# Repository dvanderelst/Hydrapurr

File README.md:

# HydraPurr

> **Running the test device?** See the tester guide:
> [`firmware/README.md`](firmware/README.md) (set-up, the screen, getting the data).

A CircuitPython device that monitors cat drinking at a water bowl. It records every touch on a wire in the water and the water level, 100 times a second, so licks and drinking bouts can be found from the data. The longer-term goal is to dispense food once a cat has completed enough drinking bouts.

(An earlier prototype, on an RP2040 board with a transistor lick circuit, RFID and live bout detection, is kept under [`legacy/`](legacy/); its firmware is documented in [`legacy/v1_firmware/README.md`](legacy/v1_firmware/README.md).)

## Project layout

```
HydraPurr/
├── HANDOFF.md    Development notes, open items and log (whole project).
├── firmware/     The device's CircuitPython code. README.md = tester guide.
├── analysis/     Data processing: fetch from the board, read, plot (own .venv).
├── pcb/          Carrier PCB (KiCad): board stack, feeder driver, connectors.
├── sync2board    Push the firmware to a connected board.
├── legacy/       The first prototype: v1_firmware/ (was BoardCode/),
│                 ProcessLickData/, CircuitSimulation/, HardwareDocs/,
│                 BluetoothDownloader/, todo.md.
└── README.md     This file.
```

## Hardware

Adafruit Feather ESP32-S3 Reverse TFT (built-in screen, WiFi) on an Adalogger FeatherWing (microSD, PCF8523 RTC), CircuitPython 10.3.1. Details, pin map and the reasoning behind each choice: [`HANDOFF.md`](HANDOFF.md).

- **Touch sensor:** a wire in the water on `D12`, read with `touchio`. A tongue (or finger) in the water raises the reading well above a slowly tracking baseline. Touching the outside of the 3D-printed resin bowl registers too, but much weaker.
- **Water level:** a float in a chimney connected to the bowl; a Sharp GP2Y0A51SK0F IR distance sensor above it on `A5` (0.62 V empty to 1.16 V full in the current bowl).
- **Contact LED** on `D9` (lit while touched; for video checks).
- **WiFi:** joins the first configured network in range; serves the SD card at `http://hydrapurr.local/`, sets its clock from NTP, and sends a heartbeat to healthchecks.io every 15 min.
- **Planned:** a carrier PCB (`pcb/`) with a 12 V boost and MOSFET driver for a feeder; bout detection and feeding back on the board (the code is in `firmware/lib/BoutDetection.py`).

## Data

The board writes hourly raw files (`raw/<date>/<hour>.csv`, every sample: touch, baseline, contact, water) and a daily events file (`events/<date>.csv`: one row per contact, a status row every 15 min, restarts, settings) to its SD card, plus `system.log`. Columns: `firmware/lib/RawRecorder.py` and `firmware/lib/EventLog.py`. Reading, fetching and plotting: [`analysis/readme.md`](analysis/readme.md).

## Development

- **Syncing code to the board:** `./sync2board firmware` — `rsync` to the mounted CIRCUITPY drive (`/media/$USER/CIRCUITPY` by default; `-d` for another path, `-n` dry run). Mirrors with `--delete` but never touches the board's `settings.toml`; excludes Python caches and editor metadata, runs `sync` afterwards. Once WiFi has been used the board does not auto-reload: press Reset (or send Ctrl-C) after syncing.
- **`analysis/`** is desktop Python — create its `.venv` from `requirements.txt` (see its readme). Entry point: `plot_hydrapurr_day.py`. Data lives in `analysis/data/v2_esp32s3_touch/` (not in git; with a README on what it holds).
- **CircuitPython `lib/` convention.** CircuitPython auto-adds `/` and `/lib` to `sys.path` on boot, so any `.py` file or package directory directly under `lib/` is importable as a top-level module (`import adafruit_pcf8523`, `from components import MySD`). Do **not** add `lib/__init__.py` — that turns `lib` into a package and breaks the standard CircuitPython import style. To get the same behaviour in PyCharm during desktop development, mark `lib/` as a Sources Root (Right-click → *Mark Directory as → Sources Root*).

## Project notes

- Notion workspace for organisation: <https://www.notion.so/PyCharm-25581ad79c6d8070aaf2cc3cb64adce6>
- The older Raspberry Pi version of HydraPurr is archived (read-only reference): <https://github.com/habit-tech/Rpi_lickometer>.

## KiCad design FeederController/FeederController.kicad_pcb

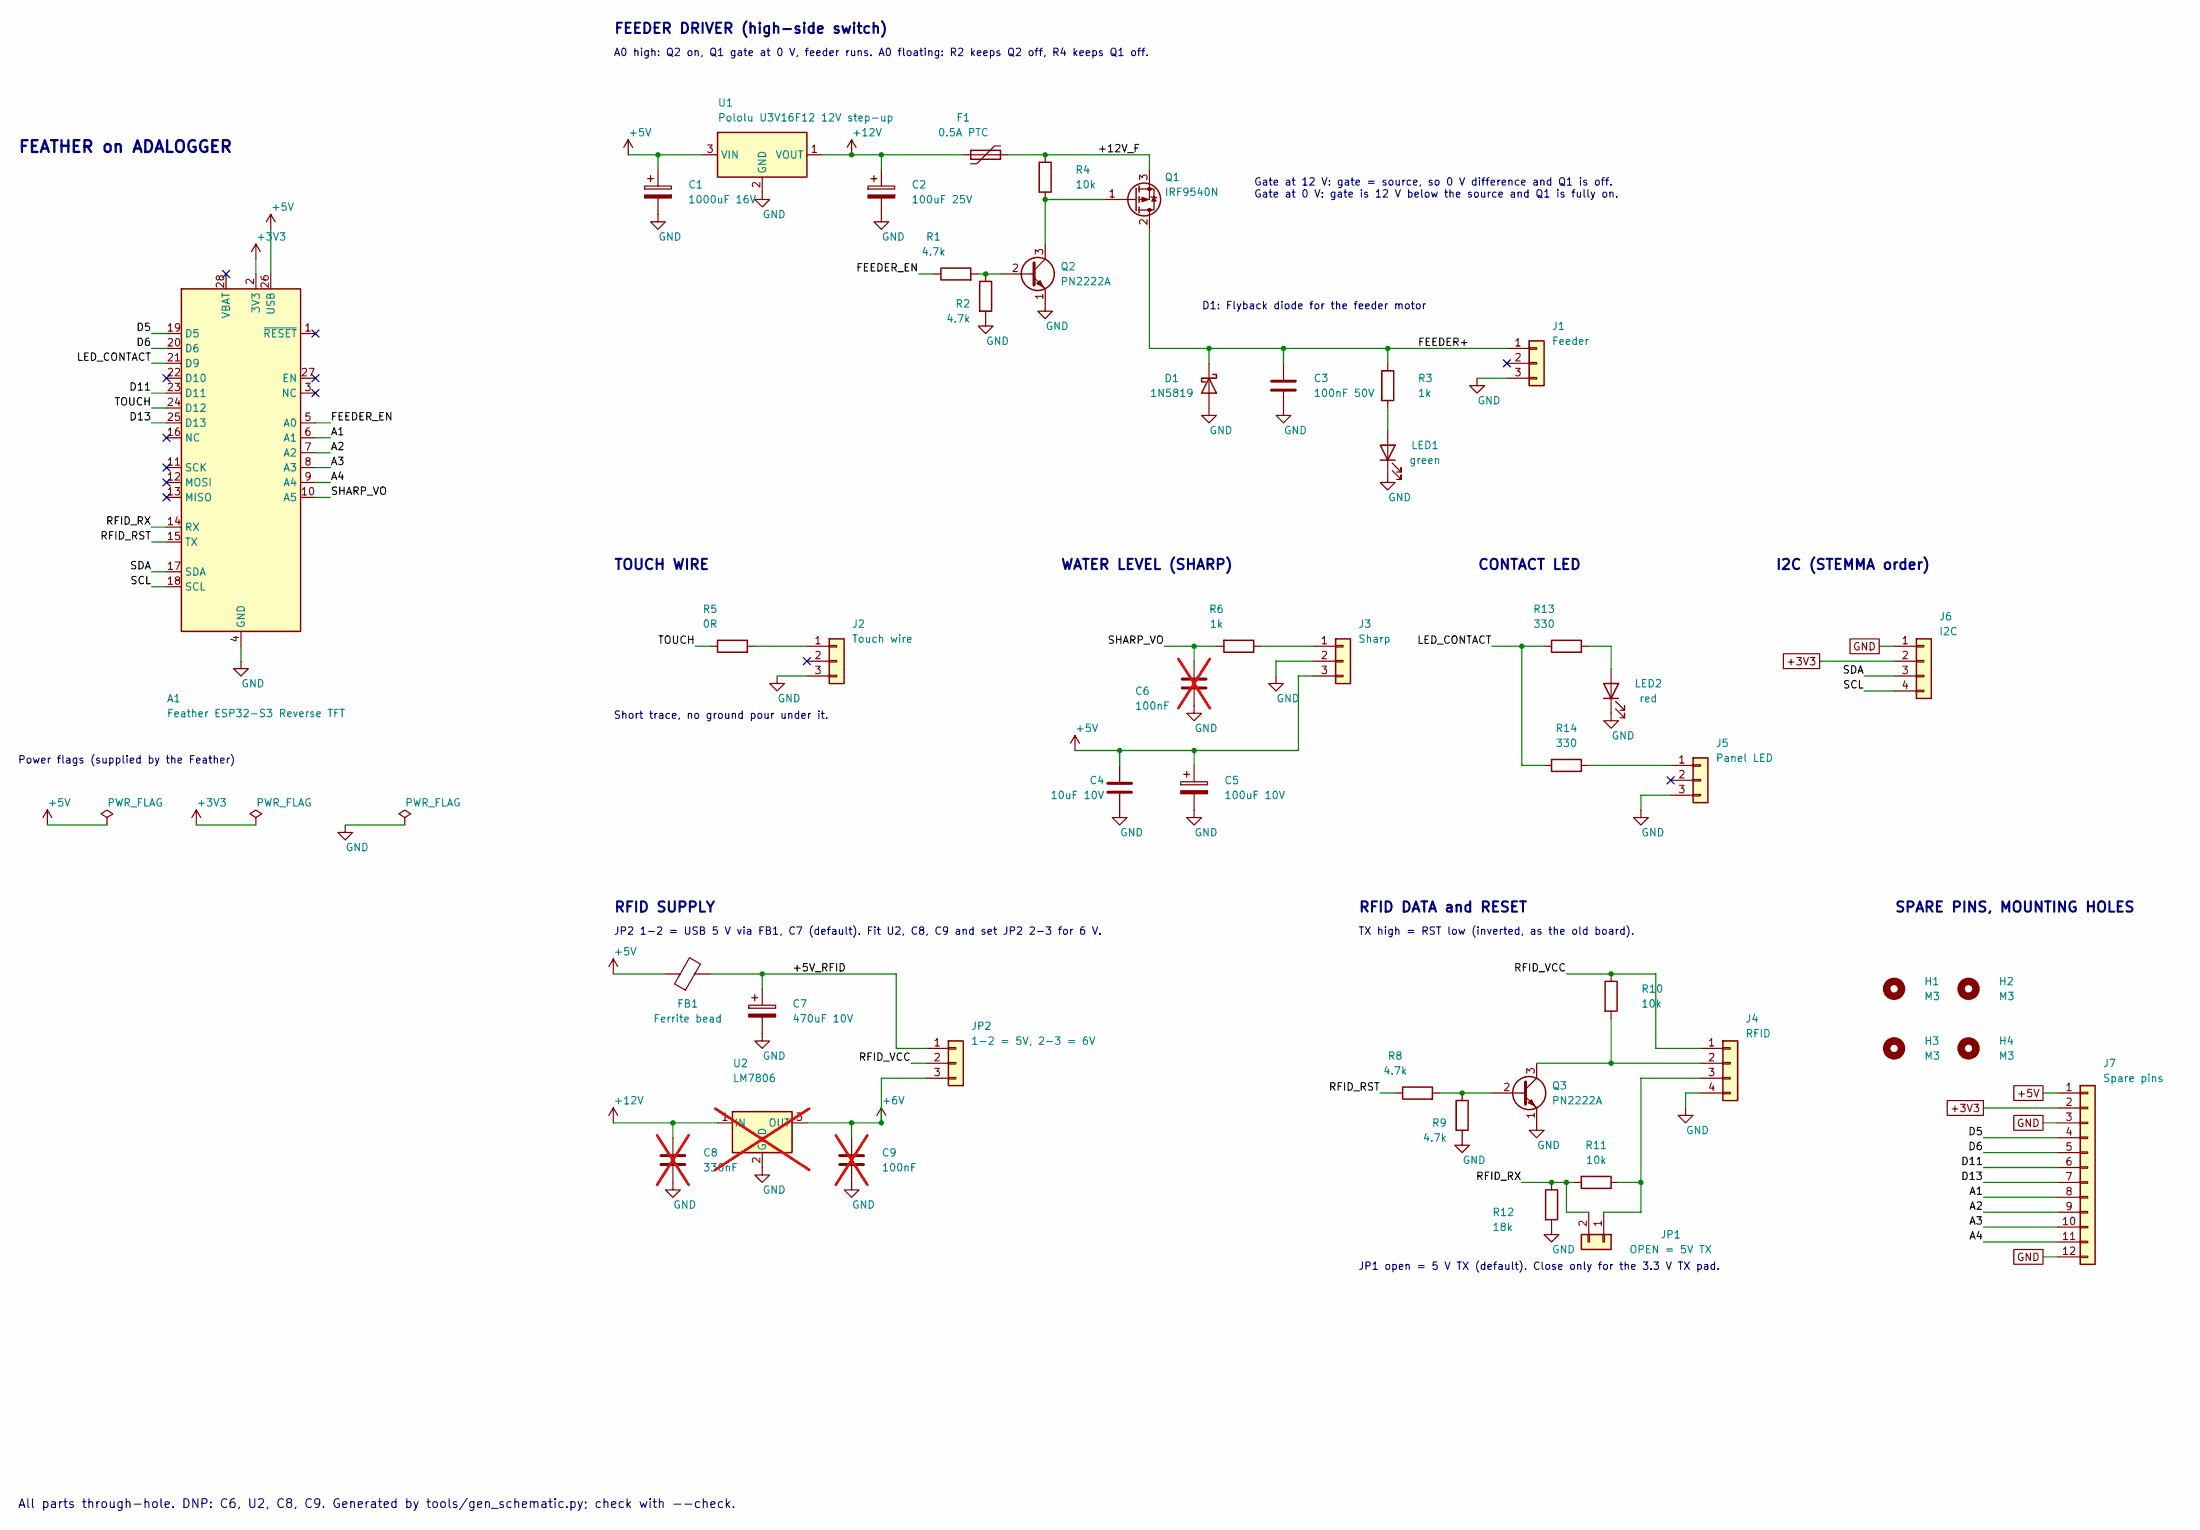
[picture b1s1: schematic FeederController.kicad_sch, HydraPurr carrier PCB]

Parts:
A1: Feather ESP32-S3 Reverse TFT; Feather_Adalogger_Inverted_Stack
C1: 1000uF 16V; CP_Radial_D10.0mm_P5.00mm
C2: 100uF 25V; CP_Radial_D6.3mm_P2.50mm
C3: 100nF 50V; C_Disc_D5.0mm_W2.5mm_P5.00mm
C4: 10uF 10V; C_Disc_D5.0mm_W2.5mm_P5.00mm
C5: 100uF 10V; CP_Radial_D6.3mm_P2.50mm
C6, C9: 100nF; C_Disc_D5.0mm_W2.5mm_P5.00mm; not fitted
C7: 470uF 10V; CP_Radial_D8.0mm_P3.50mm
C8: 330nF; C_Disc_D5.0mm_W2.5mm_P5.00mm; not fitted
D1: 1N5819; D_DO-41_SOD81_P10.16mm_Horizontal
F1: 0.5A PTC; Fuse_Bourns_MF-RHT050
FB1: Ferrite bead; L_Axial_L5.3mm_D2.2mm_P10.16mm_Horizontal_Vishay_IM-1
H1, H2, H3, H4: M3; MountingHole_3.2mm_M3
J1: Feeder; JST_PH_B3B-PH-K_1x03_P2.00mm_Vertical
J2: Touch wire; JST_PH_B3B-PH-K_1x03_P2.00mm_Vertical
J3: Sharp; JST_PH_B3B-PH-K_1x03_P2.00mm_Vertical
J4: RFID; JST_PH_B4B-PH-K_1x04_P2.00mm_Vertical
J5: Panel LED; JST_PH_B3B-PH-K_1x03_P2.00mm_Vertical
J6: I2C; JST_PH_B4B-PH-K_1x04_P2.00mm_Vertical
J7: Spare pins; PinHeader_1x12_P2.54mm_Vertical
JP1: OPEN = 5V TX; PinHeader_1x02_P2.54mm_Vertical
JP2: 1-2 = 5V, 2-3 = 6V; PinHeader_1x03_P2.54mm_Vertical
LED1: green; LED_D3.0mm
LED2: red; LED_D3.0mm
Q1: IRF9540N; TO-220-3_Vertical
Q2, Q3: PN2222A; TO-92_Inline_Wide
R1, R2, R8, R9: 4.7k; R_Axial_DIN0207_L6.3mm_D2.5mm_P10.16mm_Horizontal
R3, R6: 1k; R_Axial_DIN0207_L6.3mm_D2.5mm_P10.16mm_Horizontal
R4, R10, R11: 10k; R_Axial_DIN0207_L6.3mm_D2.5mm_P10.16mm_Horizontal
R5: 0R; R_Axial_DIN0207_L6.3mm_D2.5mm_P10.16mm_Horizontal
R12: 18k; R_Axial_DIN0207_L6.3mm_D2.5mm_P10.16mm_Horizontal
R13, R14: 330; R_Axial_DIN0207_L6.3mm_D2.5mm_P10.16mm_Horizontal
U1: Pololu U3V16F12 12V step-up; PinHeader_1x03_P2.54mm_Vertical
U2: LM7806; TO-220-3_Vertical; not fitted

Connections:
+3V3: A1.2 (3V3), J6.2, J7.2
+5V: A1.26 (USB), C1.1, C4.1, C5.1, FB1.1, J3.3, J7.1, U1.3 (VIN)
+6V: C9.1, JP2.3, U2.3 (OUT)
+12V: C2.1, C8.1, F1.1, U1.1 (VOUT), U2.1 (IN)
/+5V_RFID: C7.1, FB1.2, JP2.1
/+12V_F: F1.2, Q1.3 (S), R4.1
/A1: A1.6 (A1), J7.8
/A2: A1.7 (A2), J7.9
/A3: A1.8 (A3), J7.10
/A4: A1.9 (A4), J7.11
/D5: A1.19 (D5), J7.4
/D6: A1.20 (D6), J7.5
/D11: A1.23 (D11), J7.6
/D13: A1.25 (D13), J7.7
/FEEDER+: C3.1, D1.1 (K), J1.1, Q1.2 (D), R3.1
/FEEDER_EN: A1.5 (A0), R1.1
/LED_CONTACT: A1.21 (D9), R13.1, R14.1
/RFID_RST: A1.15 (TX), R8.1
/RFID_RX: A1.14 (RX), JP1.2, R11.2, R12.1
/RFID_VCC: J4.1, JP2.2, R10.1
/SCL: A1.18 (SCL), J6.4
/SDA: A1.17 (SDA), J6.3
/SHARP_VO: A1.10 (A5), C6.1, R6.2
/TOUCH: A1.24 (D12), R5.1
GND: A1.4 (GND), C1.2, C2.2, C3.2, C4.2, C5.2, C6.2, C7.2, C8.2, C9.2, D1.2 (A), J1.3, J2.3, J3.2, J4.4, J5.3, J6.1, J7.3, J7.12, LED1.1 (K), LED2.1 (K), Q2.1 (E), Q3.1 (E), R2.2, R9.2, R12.2, U1.2 (GND), U2.2 (GND)
unnamed: J2.1, R5.2
unnamed: J3.1, R6.1
unnamed: J4.2, Q3.3 (C), R10.2
unnamed: J4.3, JP1.1, R11.1
unnamed: J5.1, R14.2
unnamed: LED1.2 (A), R3.2
unnamed: LED2.2 (A), R13.2
unnamed: Q1.1 (G), Q2.3 (C), R4.2
unnamed: Q2.2 (B), R1.2, R2.1
unnamed: Q3.2 (B), R8.2, R9.1

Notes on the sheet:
Power flags (supplied by the Feather)
Short trace, no ground pour under it.
D1: Flyback diode for the feeder motor
All parts through-hole. DNP: C6, U2, C8, C9. Generated by tools/gen_schematic.py; check with --check.
TOUCH WIRE
JP2 1-2 = USB 5 V via FB1, C7 (default). Fit U2, C8, C9 and set JP2 2-3 for 6 V.
JP1 open = 5 V TX (default). Close only for the 3.3 V TX pad.
RFID DATA and RESET
Gate at 12 V: gate = source, so 0 V difference and Q1 is off. Gate at 0 V: gate is 12 V below the source and Q1 is fully on.
I2C (STEMMA order)
A0 high: Q2 on, Q1 gate at 0 V, feeder runs. A0 floating: R2 keeps Q2 off, R4 keeps Q1 off.
SPARE PINS, MOUNTING HOLES
FEATHER on ADALOGGER
RFID SUPPLY
FEEDER DRIVER (high-side switch)
CONTACT LED
TX high = RST low (inverted, as the old board).
WATER LEVEL (SHARP)

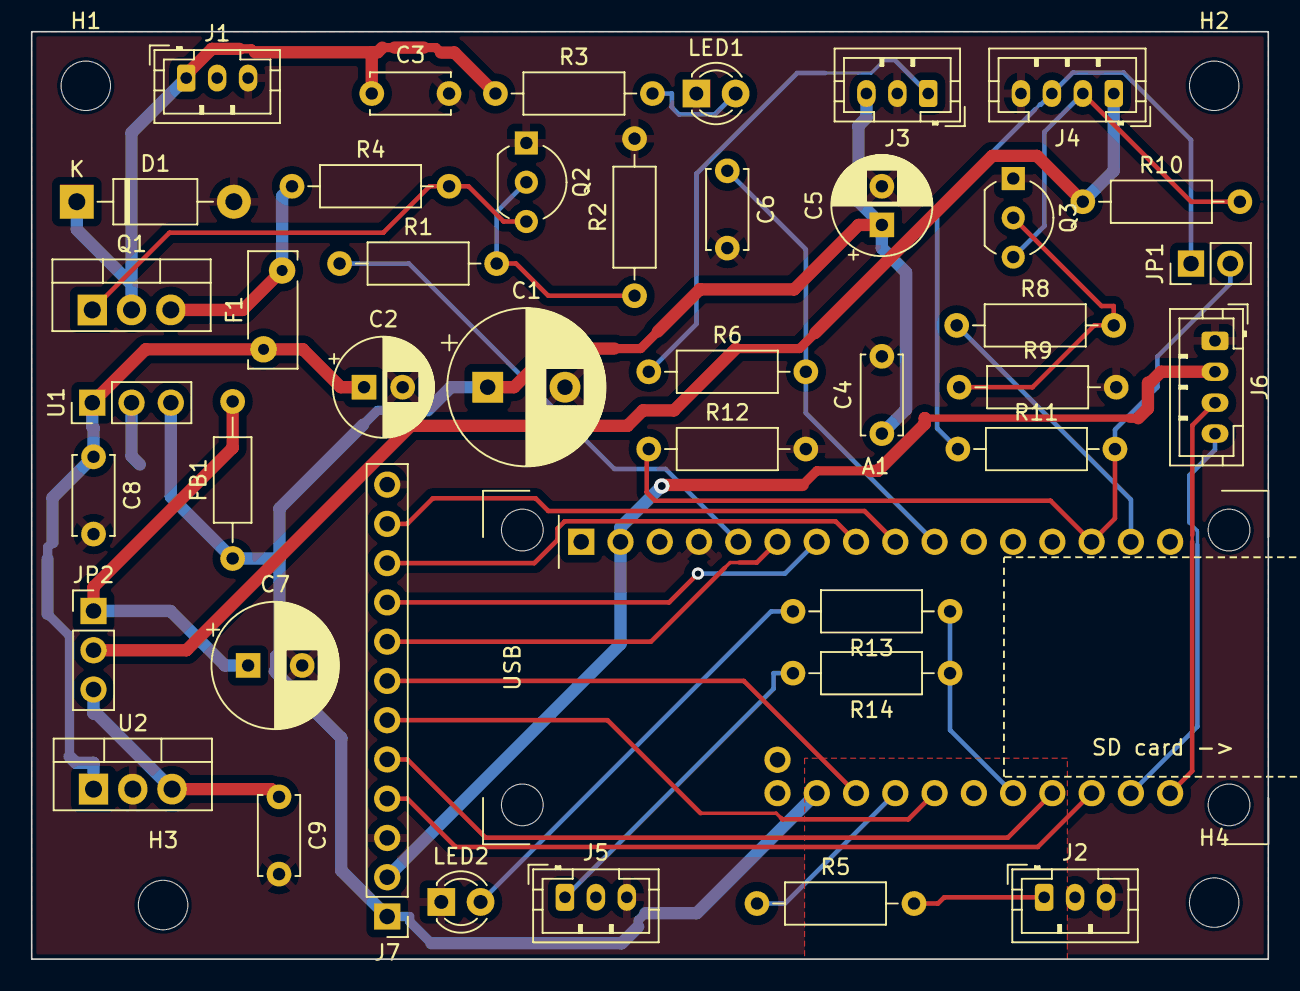
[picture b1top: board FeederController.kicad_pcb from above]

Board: 2 copper layers, 80.0 x 60.0 mm, 46 parts (0 on the bottom side), 35 nets.

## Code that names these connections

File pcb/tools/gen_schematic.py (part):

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    S.place('R1', 185.42, base_y, rot=90, refpos=(-3.81, -6.35))
    W(P('R1', 2), P('R2', 1), P('Q2', 2))
    S.pin_power('R2', 2, 'GND', 0)
    S.pin_label('R1', 1, 'FEEDER_EN')
    fp_y = 83.82
    drain = P('Q1', 2)
    S.place('D1', 228.6, fp_y + 6.35, rot=270, refpos=(-6.35, -1.27))
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    S.text(127, 121.92, 'TOUCH WIRE', 1.75)
    S.place('R5', 147.32, 134.62, rot=90, refpos=(-3.81, -6.35))
    S.place('J2', 165.1, 137.16, refpos=(2.54, -6.35))
    S.pin_label('R5', 1, 'TOUCH')
    W(P('R5', 2), P('J2', 1))
    S.nc('J2', 2)
    j = P('J2', 3)
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    S.place('C5', 226.06, 158.75)
    W(P('J3', 1), P('R6', 1))
    W(P('R6', 2), (226.06, 134.62), (220.98, 134.62))
    S.label('SHARP_VO', (220.98, 134.62), 'L')
    W((226.06, 134.62), P('C6', 1))
    S.pin_power('C6', 2, 'GND', 0)
    j = P('J3', 2)
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    S.place('R14', 289.56, 154.94, rot=90, refpos=(0, -6.35))
    S.place('J5', 312.42, 157.48, refpos=(2.54, -6.35))
    W((276.86, 134.62), (281.94, 134.62), P('R13', 1))
    S.label('LED_CONTACT', (276.86, 134.62), 'L')
    W(P('R13', 2), (P('LED2', 2)[0], 134.62), P('LED2', 2))
    S.pin_power('LED2', 1, 'GND', 0)
    W((281.94, 134.62), (281.94, 154.94), P('R14', 1))
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    S.power('+6V', (172.72, 215.9))
    W((167.64, 215.9), P('C9', 1))
    S.pin_power('C9', 2, 'GND', 0)
    S.pin_label('JP2', 2, 'RFID_VCC')

    S.text(254, 180.34, 'RFID DATA and RESET', 1.75)
    S.text(254, 184.15, 'TX high = RST low (inverted, as the old board).', 1.27, False)
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    p1, p2, p3, p4 = (P('J4', n) for n in (1, 2, 3, 4))
    S.place('R10', 297.18, 194.31)
    W(p1, (304.8, p1[1]), (304.8, 190.5), (297.18, 190.5), (289.56, 190.5))
    S.label('RFID_VCC', (289.56, 190.5), 'L')
    W(P('R10', 2), (297.18, p2[1]))
    S.place('Q3', 281.94, p2[1] + 5.08)
    W(p2, (297.18, p2[1]), P('Q3', 3))
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    S.place('R8', 264.16, qb[1], rot=90, refpos=(-3.81, -6.35))
    W(P('R8', 2), P('R9', 1), qb)
    S.pin_power('R9', 2, 'GND', 0)
    S.pin_label('R8', 1, 'RFID_RST')
    W(p3, (302.26, p3[1]), (302.26, 226.06))
    W(p4, (309.88, p4[1]), (309.88, p4[1] + 2.54))
    S.power('GND', (309.88, p4[1] + 2.54))
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    S.place('JP1', 295.91, 236.22, rot=270, refpos=(11.43, -1.27))
    W((302.26, 226.06), P('R11', 1))
    W(P('R11', 2), (289.56, 226.06), (287.02, 226.06), (281.94, 226.06))
    S.label('RFID_RX', (281.94, 226.06), 'L')
    S.pin_power('R12', 2, 'GND', 0)
    jp1, jp2 = P('JP1', 1), P('JP1', 2)
    W((302.26, 226.06), (302.26, jp1[1]), jp1)
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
